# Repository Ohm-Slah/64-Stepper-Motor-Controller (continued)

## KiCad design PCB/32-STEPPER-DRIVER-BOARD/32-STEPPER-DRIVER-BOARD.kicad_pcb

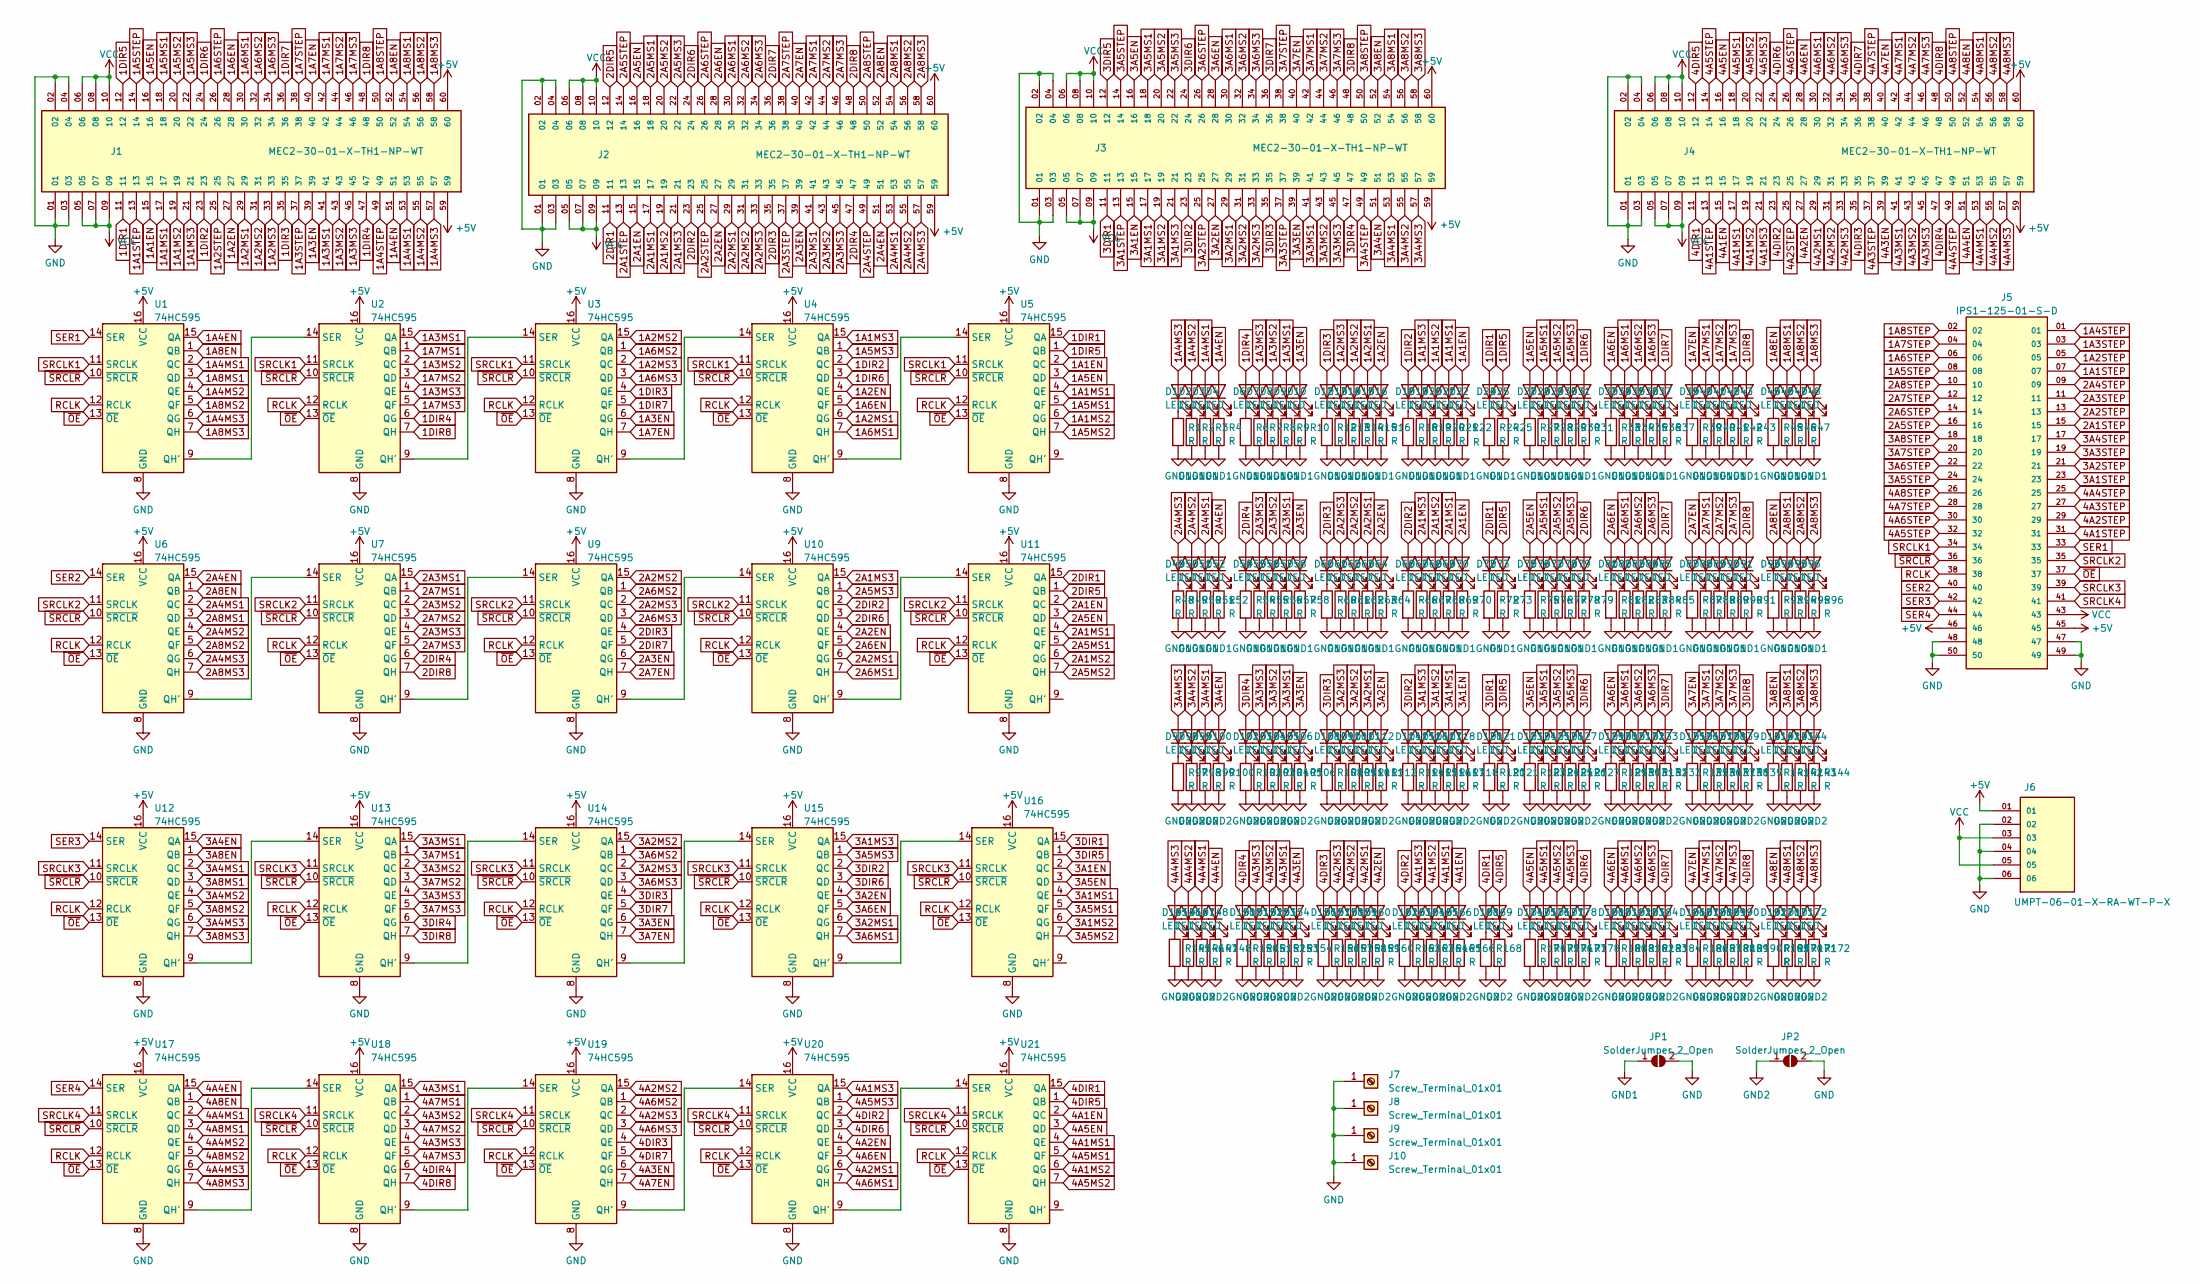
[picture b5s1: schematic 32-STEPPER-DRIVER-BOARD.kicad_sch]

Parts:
D1, D2, D3, D4, D6, D7, D8, D9, D10, D12, D13, D14, D15, D16, D18, D19, D20, D21, D22, D24, D25, D27, D28, D29, D30, D31, D33, D34, D35, D36, D37, D39, D40, D41, D42, D43, D45, D46, D47, D48, D49, D50, D51, D52, D54, D55, D56, D57, D58, D60, D61, D62, D63, D64, D66, D67, D68, D69, D70, D72, D73, D75, D76, D77, D78, D79, D81, D82, D83, D84, D85, D87, D88, D89, D90, D91, D93, D94, D95, D96, D97, D98, D99, D100, D102, D103, D104, D105, D106, D108, D109, D110, D111, D112, D114, D115, D116, D117, D118, D120, D121, D123, D124, D125, D126, D127, D129, D130, D131, D132, D133, D135, D136, D137, D138, D139, D141, D142, D143, D144, D145, D146, D147, D148, D150, D151, D152, D153, D154, D156, D157, D158, D159, D160, D162, D163, D164, D165, D166, D168, D169, D170, D171, D172, D174, D175, D176, D177, D178, D180, D181, D182, D183, D184, D186, D187, D188, D189, D190, D192: LED; LED_0603_1608Metric
J1, J2, J3, J4: MEC2-30-01-X-TH1-NP-WT; SAMTEC_MEC2-30-01-X-TH1-NP-WT; PARTREV F
J5: IPS1-125-01-S-D; SAMTEC_IPS1-125-01-S-D; PARTREV R
J6: UMPT-06-01-X-RA-WT-P-X; SAMTEC_UMPT-06-01-X-RA-WT-P-X; PARTREV 4
J7, J8, J9, J10: Screw_Terminal_01x01; MountingHole_2.2mm_M2_Pad
JP1, JP2: SolderJumper_2_Open; SolderJumper-2_P1.3mm_Open_RoundedPad1.0x1.5mm
R1, R2, R3, R4, R6, R7, R8, R9, R10, R12, R13, R14, R15, R16, R18, R19, R20, R21, R22, R24, R25, R27, R28, R29, R30, R31, R33, R34, R35, R36, R37, R39, R40, R41, R42, R43, R45, R46, R47, R48, R49, R50, R51, R52, R54, R55, R56, R57, R58, R60, R61, R62, R63, R64, R66, R67, R68, R69, R70, R72, R73, R75, R76, R77, R78, R79, R81, R82, R83, R84, R85, R87, R88, R89, R90, R91, R93, R94, R95, R96, R97, R98, R99, R100, R102, R103, R104, R105, R106, R108, R109, R110, R111, R112, R114, R115, R116, R117, R118, R120, R121, R123, R124, R125, R126, R127, R129, R130, R131, R132, R133, R135, R136, R137, R138, R139, R141, R142, R143, R144, R145, R146, R147, R148, R150, R151, R152, R153, R154, R156, R157, R158, R159, R160, R162, R163, R164, R165, R166, R168, R169, R170, R171, R172, R174, R175, R176, R177, R178, R180, R181, R182, R183, R184, R186, R187, R188, R189, R190, R192: R; R_0603_1608Metric
U1, U2, U3, U4, U5, U6, U7, U9, U10, U11, U12, U13, U14, U15, U16, U17, U18, U19, U20, U21: 74HC595; TSSOP-16_4.4x5mm_P0.65mm

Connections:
1A1EN: D22.2 (A), J1.15, U5.2 (QC)
1A1MS1: D21.2 (A), J1.17, U5.4 (QE)
1A1MS2: D20.2 (A), J1.19, U5.6 (QG)
1A1MS3: D19.2 (A), J1.21, U4.15 (QA)
1A1STEP: J1.13, J5.07
1A2EN: D16.2 (A), J1.27, U4.4 (QE)
1A2MS1: D15.2 (A), J1.29, U4.6 (QG)
1A2MS2: D14.2 (A), J1.31, U3.15 (QA)
1A2MS3: D13.2 (A), J1.33, U3.2 (QC)
1A2STEP: J1.25, J5.05
1A3EN: D10.2 (A), J1.39, U3.6 (QG)
1A3MS1: D9.2 (A), J1.41, U2.15 (QA)
1A3MS2: D8.2 (A), J1.43, U2.2 (QC)
1A3MS3: D7.2 (A), J1.45, U2.4 (QE)
1A3STEP: J1.37, J5.03
1A4EN: D4.2 (A), J1.51, U1.15 (QA)
1A4MS1: D3.2 (A), J1.53, U1.2 (QC)
1A4MS2: D2.2 (A), J1.55, U1.4 (QE)
1A4MS3: D1.2 (A), J1.57, U1.6 (QG)
1A4STEP: J1.49, J5.01
1A5EN: D27.2 (A), J1.16, U5.3 (QD)
1A5MS1: D28.2 (A), J1.18, U5.5 (QF)
1A5MS2: D29.2 (A), J1.20, U5.7 (QH)
1A5MS3: D30.2 (A), J1.22, U4.1 (QB)
1A5STEP: J1.14, J5.08
1A6EN: D33.2 (A), J1.28, U4.5 (QF)
1A6MS1: D34.2 (A), J1.30, U4.7 (QH)
1A6MS2: D35.2 (A), J1.32, U3.1 (QB)
1A6MS3: D36.2 (A), J1.34, U3.3 (QD)
1A6STEP: J1.26, J5.06
1A7EN: D39.2 (A), J1.40, U3.7 (QH)
1A7MS1: D40.2 (A), J1.42, U2.1 (QB)
1A7MS2: D41.2 (A), J1.44, U2.3 (QD)
1A7MS3: D42.2 (A), J1.46, U2.5 (QF)
1A7STEP: J1.38, J5.04
1A8EN: D45.2 (A), J1.52, U1.1 (QB)
1A8MS1: D46.2 (A), J1.54, U1.3 (QD)
1A8MS2: D47.2 (A), J1.56, U1.5 (QF)
1A8MS3: D48.2 (A), J1.58, U1.7 (QH)
1A8STEP: J1.50, J5.02
1DIR1: D24.2 (A), J1.11, U5.15 (QA)
1DIR2: D18.2 (A), J1.23, U4.2 (QC)
1DIR3: D12.2 (A), J1.35, U3.4 (QE)
1DIR4: D6.2 (A), J1.47, U2.6 (QG)
1DIR5: D25.2 (A), J1.12, U5.1 (QB)
1DIR6: D31.2 (A), J1.24, U4.3 (QD)
1DIR7: D37.2 (A), J1.36, U3.5 (QF)
1DIR8: D43.2 (A), J1.48, U2.7 (QH)
2A1EN: D70.2 (A), J2.15, U11.2 (QC)
2A1MS1: D69.2 (A), J2.17, U11.4 (QE)
2A1MS2: D68.2 (A), J2.19, U11.6 (QG)
2A1MS3: D67.2 (A), J2.21, U10.15 (QA)
2A1STEP: J2.13, J5.15
2A2EN: D64.2 (A), J2.27, U10.4 (QE)
2A2MS1: D63.2 (A), J2.29, U10.6 (QG)
2A2MS2: D62.2 (A), J2.31, U9.15 (QA)
2A2MS3: D61.2 (A), J2.33, U9.2 (QC)
2A2STEP: J2.25, J5.13
2A3EN: D58.2 (A), J2.39, U9.6 (QG)
2A3MS1: D57.2 (A), J2.41, U7.15 (QA)
2A3MS2: D56.2 (A), J2.43, U7.2 (QC)
2A3MS3: D55.2 (A), J2.45, U7.4 (QE)
2A3STEP: J2.37, J5.11
2A4EN: D52.2 (A), J2.51, U6.15 (QA)
2A4MS1: D51.2 (A), J2.53, U6.2 (QC)
2A4MS2: D50.2 (A), J2.55, U6.4 (QE)
2A4MS3: D49.2 (A), J2.57, U6.6 (QG)
2A4STEP: J2.49, J5.09
2A5EN: D75.2 (A), J2.16, U11.3 (QD)
2A5MS1: D76.2 (A), J2.18, U11.5 (QF)
2A5MS2: D77.2 (A), J2.20, U11.7 (QH)
2A5MS3: D78.2 (A), J2.22, U10.1 (QB)
2A5STEP: J2.14, J5.16
2A6EN: D81.2 (A), J2.28, U10.5 (QF)
2A6MS1: D82.2 (A), J2.30, U10.7 (QH)
2A6MS2: D83.2 (A), J2.32, U9.1 (QB)
2A6MS3: D84.2 (A), J2.34, U9.3 (QD)
2A6STEP: J2.26, J5.14
2A7EN: D87.2 (A), J2.40, U9.7 (QH)
2A7MS1: D88.2 (A), J2.42, U7.1 (QB)
2A7MS2: D89.2 (A), J2.44, U7.3 (QD)
2A7MS3: D90.2 (A), J2.46, U7.5 (QF)
2A7STEP: J2.38, J5.12
2A8EN: D93.2 (A), J2.52, U6.1 (QB)
2A8MS1: D94.2 (A), J2.54, U6.3 (QD)
2A8MS2: D95.2 (A), J2.56, U6.5 (QF)
2A8MS3: D96.2 (A), J2.58, U6.7 (QH)
2A8STEP: J2.50, J5.10
2DIR1: D72.2 (A), J2.11, U11.15 (QA)
2DIR2: D66.2 (A), J2.23, U10.2 (QC)
2DIR3: D60.2 (A), J2.35, U9.4 (QE)
2DIR4: D54.2 (A), J2.47, U7.6 (QG)
2DIR5: D73.2 (A), J2.12, U11.1 (QB)
2DIR6: D79.2 (A), J2.24, U10.3 (QD)
2DIR7: D85.2 (A), J2.36, U9.5 (QF)
2DIR8: D91.2 (A), J2.48, U7.7 (QH)
3A1EN: D118.2 (A), J3.15, U16.2 (QC)
3A1MS1: D117.2 (A), J3.17, U16.4 (QE)
3A1MS2: D116.2 (A), J3.19, U16.6 (QG)
3A1MS3: D115.2 (A), J3.21, U15.15 (QA)
3A1STEP: J3.13, J5.23
3A2EN: D112.2 (A), J3.27, U15.4 (QE)
3A2MS1: D111.2 (A), J3.29, U15.6 (QG)
3A2MS2: D110.2 (A), J3.31, U14.15 (QA)
3A2MS3: D109.2 (A), J3.33, U14.2 (QC)
3A2STEP: J3.25, J5.21
3A3EN: D106.2 (A), J3.39, U14.6 (QG)
3A3MS1: D105.2 (A), J3.41, U13.15 (QA)
3A3MS2: D104.2 (A), J3.43, U13.2 (QC)
3A3MS3: D103.2 (A), J3.45, U13.4 (QE)
3A3STEP: J3.37, J5.19
3A4EN: D100.2 (A), J3.51, U12.15 (QA)
3A4MS1: D99.2 (A), J3.53, U12.2 (QC)
3A4MS2: D98.2 (A), J3.55, U12.4 (QE)
3A4MS3: D97.2 (A), J3.57, U12.6 (QG)
3A4STEP: J3.49, J5.17
3A5EN: D123.2 (A), J3.16, U16.3 (QD)
3A5MS1: D124.2 (A), J3.18, U16.5 (QF)
3A5MS2: D125.2 (A), J3.20, U16.7 (QH)
3A5MS3: D126.2 (A), J3.22, U15.1 (QB)
3A5STEP: J3.14, J5.24
3A6EN: D129.2 (A), J3.28, U15.5 (QF)
3A6MS1: D130.2 (A), J3.30, U15.7 (QH)
3A6MS2: D131.2 (A), J3.32, U14.1 (QB)
3A6MS3: D132.2 (A), J3.34, U14.3 (QD)
3A6STEP: J3.26, J5.22
3A7EN: D135.2 (A), J3.40, U14.7 (QH)
3A7MS1: D136.2 (A), J3.42, U13.1 (QB)
3A7MS2: D137.2 (A), J3.44, U13.3 (QD)
3A7MS3: D138.2 (A), J3.46, U13.5 (QF)
3A7STEP: J3.38, J5.20
3A8EN: D141.2 (A), J3.52, U12.1 (QB)
3A8MS1: D142.2 (A), J3.54, U12.3 (QD)
3A8MS2: D143.2 (A), J3.56, U12.5 (QF)
3A8MS3: D144.2 (A), J3.58, U12.7 (QH)
3A8STEP: J3.50, J5.18
3DIR1: D120.2 (A), J3.11, U16.15 (QA)
3DIR2: D114.2 (A), J3.23, U15.2 (QC)
3DIR3: D108.2 (A), J3.35, U14.4 (QE)
3DIR4: D102.2 (A), J3.47, U13.6 (QG)
3DIR5: D121.2 (A), J3.12, U16.1 (QB)
3DIR6: D127.2 (A), J3.24, U15.3 (QD)
3DIR7: D133.2 (A), J3.36, U14.5 (QF)
3DIR8: D139.2 (A), J3.48, U13.7 (QH)
4A1EN: D166.2 (A), J4.15, U21.2 (QC)
4A1MS1: D165.2 (A), J4.17, U21.4 (QE)
4A1MS2: D164.2 (A), J4.19, U21.6 (QG)
4A1MS3: D163.2 (A), J4.21, U20.15 (QA)
4A1STEP: J4.13, J5.31
4A2EN: D160.2 (A), J4.27, U20.4 (QE)
4A2MS1: D159.2 (A), J4.29, U20.6 (QG)
4A2MS2: D158.2 (A), J4.31, U19.15 (QA)
4A2MS3: D157.2 (A), J4.33, U19.2 (QC)
4A2STEP: J4.25, J5.29
4A3EN: D154.2 (A), J4.39, U19.6 (QG)
4A3MS1: D153.2 (A), J4.41, U18.15 (QA)
4A3MS2: D152.2 (A), J4.43, U18.2 (QC)
4A3MS3: D151.2 (A), J4.45, U18.4 (QE)
4A3STEP: J4.37, J5.27
4A4EN: D148.2 (A), J4.51, U17.15 (QA)
4A4MS1: D147.2 (A), J4.53, U17.2 (QC)
4A4MS2: D146.2 (A), J4.55, U17.4 (QE)
4A4MS3: D145.2 (A), J4.57, U17.6 (QG)
4A4STEP: J4.49, J5.25
4A5EN: D174.2 (A), J4.16, U21.3 (QD)
4A5MS1: D175.2 (A), J4.18, U21.5 (QF)
4A5MS2: D176.2 (A), J4.20, U21.7 (QH)
4A5MS3: D177.2 (A), J4.22, U20.1 (QB)
4A5STEP: J4.14, J5.32
4A6EN: D180.2 (A), J4.28, U20.5 (QF)
4A6MS1: D181.2 (A), J4.30, U20.7 (QH)
4A6MS2: D182.2 (A), J4.32, U19.1 (QB)
4A6MS3: D183.2 (A), J4.34, U19.3 (QD)
4A6STEP: J4.26, J5.30
4A7EN: D186.2 (A), J4.40, U19.7 (QH)
4A7MS1: D187.2 (A), J4.42, U18.1 (QB)
4A7MS2: D188.2 (A), J4.44, U18.3 (QD)
4A7MS3: D189.2 (A), J4.46, U18.5 (QF)
4A7STEP: J4.38, J5.28
4A8EN: D192.2 (A), J4.52, U17.1 (QB)
4A8MS1: D170.2 (A), J4.54, U17.3 (QD)
4A8MS2: D171.2 (A), J4.56, U17.5 (QF)
4A8MS3: D172.2 (A), J4.58, U17.7 (QH)
4A8STEP: J4.50, J5.26
4DIR1: D168.2 (A), J4.11, U21.15 (QA)
4DIR2: D162.2 (A), J4.23, U20.2 (QC)
4DIR3: D156.2 (A), J4.35, U19.4 (QE)
4DIR4: D150.2 (A), J4.47, U18.6 (QG)
4DIR5: D169.2 (A), J4.12, U21.1 (QB)
4DIR6: D178.2 (A), J4.24, U20.3 (QD)
4DIR7: D184.2 (A), J4.36, U19.5 (QF)
4DIR8: D190.2 (A), J4.48, U18.7 (QH)
+5V: J1.59, J1.60, J2.59, J2.60, J3.59, J3.60, J4.59, J4.60, J5.45, J5.46, J6.01, U1.16 (VCC), U2.16 (VCC), U3.16 (VCC), U4.16 (VCC), U5.16 (VCC), U6.16 (VCC), U7.16 (VCC), U9.16 (VCC), U10.16 (VCC), U11.16 (VCC), U12.16 (VCC), U13.16 (VCC), U14.16 (VCC), U15.16 (VCC), U16.16 (VCC), U17.16 (VCC), U18.16 (VCC), U19.16 (VCC), U20.16 (VCC), U21.16 (VCC)
GND: J1.01, J1.02, J1.03, J1.04, J2.01, J2.02, J2.03, J2.04, J3.01, J3.02, J3.03, J3.04, J4.01, J4.02, J4.03, J4.04, J5.47, J5.48, J5.49, J5.50, J6.02, J6.04, J6.06, J7.1, J8.1, J9.1, J10.1, JP1.2 (B), JP2.2 (B), U1.8 (GND), U2.8 (GND), U3.8 (GND), U4.8 (GND), U5.8 (GND), U6.8 (GND), U7.8 (GND), U9.8 (GND), U10.8 (GND), U11.8 (GND), U12.8 (GND), U13.8 (GND), U14.8 (GND), U15.8 (GND), U16.8 (GND), U17.8 (GND), U18.8 (GND), U19.8 (GND), U20.8 (GND), U21.8 (GND)
GND1: JP1.1 (A), R1.2, R2.2, R3.2, R4.2, R6.2, R7.2, R8.2, R9.2, R10.2, R12.2, R13.2, R14.2, R15.2, R16.2, R18.2, R19.2, R20.2, R21.2, R22.2, R24.2, R25.2, R27.2, R28.2, R29.2, R30.2, R31.2, R33.2, R34.2, R35.2, R36.2, R37.2, R39.2, R40.2, R41.2, R42.2, R43.2, R45.2, R46.2, R47.2, R48.2, R49.2, R50.2, R51.2, R52.2, R54.2, R55.2, R56.2, R57.2, R58.2, R60.2, R61.2, R62.2, R63.2, R64.2, R66.2, R67.2, R68.2, R69.2, R70.2, R72.2, R73.2, R75.2, R76.2, R77.2, R78.2, R79.2, R81.2, R82.2, R83.2, R84.2, R85.2, R87.2, R88.2, R89.2, R90.2, R91.2, R93.2, R94.2, R95.2, R96.2
GND2: JP2.1 (A), R97.2, R98.2, R99.2, R100.2, R102.2, R103.2, R104.2, R105.2, R106.2, R108.2, R109.2, R110.2, R111.2, R112.2, R114.2, R115.2, R116.2, R117.2, R118.2, R120.2, R121.2, R123.2, R124.2, R125.2, R126.2, R127.2, R129.2, R130.2, R131.2, R132.2, R133.2, R135.2, R136.2, R137.2, R138.2, R139.2, R141.2, R142.2, R143.2, R144.2, R145.2, R146.2, R147.2, R148.2, R150.2, R151.2, R152.2, R153.2, R154.2, R156.2, R157.2, R158.2, R159.2, R160.2, R162.2, R163.2, R164.2, R165.2, R166.2, R168.2, R169.2, R170.2, R171.2, R172.2, R174.2, R175.2, R176.2, R177.2, R178.2, R180.2, R181.2, R182.2, R183.2, R184.2, R186.2, R187.2, R188.2, R189.2, R190.2, R192.2
unnamed: D1.1 (K), R1.1
unnamed: D2.1 (K), R2.1
unnamed: D3.1 (K), R3.1
unnamed: D4.1 (K), R4.1
unnamed: D6.1 (K), R6.1
unnamed: D7.1 (K), R7.1
unnamed: D8.1 (K), R8.1
unnamed: D9.1 (K), R9.1
unnamed: D10.1 (K), R10.1
unnamed: D12.1 (K), R12.1
unnamed: D13.1 (K), R13.1
unnamed: D14.1 (K), R14.1
unnamed: D15.1 (K), R15.1
unnamed: D16.1 (K), R16.1
unnamed: D18.1 (K), R18.1
unnamed: D19.1 (K), R19.1
unnamed: D20.1 (K), R20.1
unnamed: D21.1 (K), R21.1
unnamed: D22.1 (K), R22.1
unnamed: D24.1 (K), R24.1
unnamed: D25.1 (K), R25.1
unnamed: D27.1 (K), R27.1
unnamed: D28.1 (K), R28.1
unnamed: D29.1 (K), R29.1
unnamed: D30.1 (K), R30.1
unnamed: D31.1 (K), R31.1
unnamed: D33.1 (K), R33.1
unnamed: D34.1 (K), R34.1
unnamed: D35.1 (K), R35.1
unnamed: D36.1 (K), R36.1
unnamed: D37.1 (K), R37.1
unnamed: D39.1 (K), R39.1
unnamed: D40.1 (K), R40.1
unnamed: D41.1 (K), R41.1
unnamed: D42.1 (K), R42.1
unnamed: D43.1 (K), R43.1
unnamed: D45.1 (K), R45.1
unnamed: D46.1 (K), R46.1
unnamed: D47.1 (K), R47.1
unnamed: D48.1 (K), R48.1
unnamed: D49.1 (K), R49.1
unnamed: D50.1 (K), R50.1
unnamed: D51.1 (K), R51.1
unnamed: D52.1 (K), R52.1
unnamed: D54.1 (K), R54.1
unnamed: D55.1 (K), R55.1
unnamed: D56.1 (K), R56.1
unnamed: D57.1 (K), R57.1
unnamed: D58.1 (K), R58.1
unnamed: D60.1 (K), R60.1
unnamed: D61.1 (K), R61.1
unnamed: D62.1 (K), R62.1
unnamed: D63.1 (K), R63.1
unnamed: D64.1 (K), R64.1
unnamed: D66.1 (K), R66.1
unnamed: D67.1 (K), R67.1
unnamed: D68.1 (K), R68.1
unnamed: D69.1 (K), R69.1
unnamed: D70.1 (K), R70.1
unnamed: D72.1 (K), R72.1
unnamed: D73.1 (K), R73.1
unnamed: D75.1 (K), R75.1
unnamed: D76.1 (K), R76.1
unnamed: D77.1 (K), R77.1
unnamed: D78.1 (K), R78.1
unnamed: D79.1 (K), R79.1
unnamed: D81.1 (K), R81.1
unnamed: D82.1 (K), R82.1
unnamed: D83.1 (K), R83.1
unnamed: D84.1 (K), R84.1
unnamed: D85.1 (K), R85.1
unnamed: D87.1 (K), R87.1
unnamed: D88.1 (K), R88.1
unnamed: D89.1 (K), R89.1
unnamed: D90.1 (K), R90.1
unnamed: D91.1 (K), R91.1
unnamed: D93.1 (K), R93.1
unnamed: D94.1 (K), R94.1
unnamed: D95.1 (K), R95.1
unnamed: D96.1 (K), R96.1
unnamed: D97.1 (K), R97.1
unnamed: D98.1 (K), R98.1
unnamed: D99.1 (K), R99.1
unnamed: D100.1 (K), R100.1
unnamed: D102.1 (K), R102.1
unnamed: D103.1 (K), R103.1
unnamed: D104.1 (K), R104.1
unnamed: D105.1 (K), R105.1
unnamed: D106.1 (K), R106.1
unnamed: D108.1 (K), R108.1
unnamed: D109.1 (K), R109.1
unnamed: D110.1 (K), R110.1
unnamed: D111.1 (K), R111.1
unnamed: D112.1 (K), R112.1
unnamed: D114.1 (K), R114.1
unnamed: D115.1 (K), R115.1
unnamed: D116.1 (K), R116.1
unnamed: D117.1 (K), R117.1
unnamed: D118.1 (K), R118.1
unnamed: D120.1 (K), R120.1
unnamed: D121.1 (K), R121.1
unnamed: D123.1 (K), R123.1
unnamed: D124.1 (K), R124.1
unnamed: D125.1 (K), R125.1
unnamed: D126.1 (K), R126.1
unnamed: D127.1 (K), R127.1
unnamed: D129.1 (K), R129.1
unnamed: D130.1 (K), R130.1
unnamed: D131.1 (K), R131.1
unnamed: D132.1 (K), R132.1
unnamed: D133.1 (K), R133.1
unnamed: D135.1 (K), R135.1
unnamed: D136.1 (K), R136.1
unnamed: D137.1 (K), R137.1
unnamed: D138.1 (K), R138.1
unnamed: D139.1 (K), R139.1
unnamed: D141.1 (K), R141.1
unnamed: D142.1 (K), R142.1
unnamed: D143.1 (K), R143.1
unnamed: D144.1 (K), R144.1
unnamed: D145.1 (K), R145.1
unnamed: D146.1 (K), R146.1
unnamed: D147.1 (K), R147.1
unnamed: D148.1 (K), R148.1
unnamed: D150.1 (K), R150.1
unnamed: D151.1 (K), R151.1
unnamed: D152.1 (K), R152.1
unnamed: D153.1 (K), R153.1
unnamed: D154.1 (K), R154.1
unnamed: D156.1 (K), R156.1
unnamed: D157.1 (K), R157.1
unnamed: D158.1 (K), R158.1
unnamed: D159.1 (K), R159.1
unnamed: D160.1 (K), R160.1
unnamed: D162.1 (K), R162.1
unnamed: D163.1 (K), R163.1
unnamed: D164.1 (K), R164.1
unnamed: D165.1 (K), R165.1
unnamed: D166.1 (K), R166.1
unnamed: D168.1 (K), R168.1
unnamed: D169.1 (K), R169.1
unnamed: D170.1 (K), R170.1
unnamed: D171.1 (K), R171.1
unnamed: D172.1 (K), R172.1
unnamed: D174.1 (K), R174.1
unnamed: D175.1 (K), R175.1
unnamed: D176.1 (K), R176.1
unnamed: D177.1 (K), R177.1
unnamed: D178.1 (K), R178.1
unnamed: D180.1 (K), R180.1
unnamed: D181.1 (K), R181.1
unnamed: D182.1 (K), R182.1
unnamed: D183.1 (K), R183.1
unnamed: D184.1 (K), R184.1
unnamed: D186.1 (K), R186.1
unnamed: D187.1 (K), R187.1
unnamed: D188.1 (K), R188.1
unnamed: D189.1 (K), R189.1
unnamed: D190.1 (K), R190.1
unnamed: D192.1 (K), R192.1
unnamed: U1.9 (QH'), U2.14 (SER)
unnamed: U2.9 (QH'), U3.14 (SER)
unnamed: U3.9 (QH'), U4.14 (SER)
unnamed: U4.9 (QH'), U5.14 (SER)
unnamed: U6.9 (QH'), U7.14 (SER)
unnamed: U7.9 (QH'), U9.14 (SER)
unnamed: U10.9 (QH'), U11.14 (SER)
unnamed: U9.9 (QH'), U10.14 (SER)
unnamed: U12.9 (QH'), U13.14 (SER)
unnamed: U13.9 (QH'), U14.14 (SER)
unnamed: U14.9 (QH'), U15.14 (SER)
unnamed: U15.9 (QH'), U16.14 (SER)
unnamed: U17.9 (QH'), U18.14 (SER)
unnamed: U18.9 (QH'), U19.14 (SER)
unnamed: U19.9 (QH'), U20.14 (SER)
unnamed: U20.9 (QH'), U21.14 (SER)
RCLK: J5.38, U1.12 (RCLK), U2.12 (RCLK), U3.12 (RCLK), U4.12 (RCLK), U5.12 (RCLK), U6.12 (RCLK), U7.12 (RCLK), U9.12 (RCLK), U10.12 (RCLK), U11.12 (RCLK), U12.12 (RCLK), U13.12 (RCLK), U14.12 (RCLK), U15.12 (RCLK), U16.12 (RCLK), U17.12 (RCLK), U18.12 (RCLK), U19.12 (RCLK), U20.12 (RCLK), U21.12 (RCLK)
SER1: J5.33, U1.14 (SER)
SER2: J5.40, U6.14 (SER)
SER3: J5.42, U12.14 (SER)
SER4: J5.44, U17.14 (SER)
SRCLK1: J5.34, U1.11 (SRCLK), U2.11 (SRCLK), U3.11 (SRCLK), U4.11 (SRCLK), U5.11 (SRCLK)
SRCLK2: J5.35, U6.11 (SRCLK), U7.11 (SRCLK), U9.11 (SRCLK), U10.11 (SRCLK), U11.11 (SRCLK)
SRCLK3: J5.39, U12.11 (SRCLK), U13.11 (SRCLK), U14.11 (SRCLK), U15.11 (SRCLK), U16.11 (SRCLK)
SRCLK4: J5.41, U17.11 (SRCLK), U18.11 (SRCLK), U19.11 (SRCLK), U20.11 (SRCLK), U21.11 (SRCLK)
VCC: J1.05, J1.06, J1.07, J1.08, J1.09, J1.10, J2.05, J2.06, J2.07, J2.08, J2.09, J2.10, J3.05, J3.06, J3.07, J3.08, J3.09, J3.10, J4.05, J4.06, J4.07, J4.08, J4.09, J4.10, J5.43, J6.03, J6.05
~OE: J5.37, U1.13 (~OE), U2.13 (~OE), U3.13 (~OE), U4.13 (~OE), U5.13 (~OE), U6.13 (~OE), U7.13 (~OE), U9.13 (~OE), U10.13 (~OE), U11.13 (~OE), U12.13 (~OE), U13.13 (~OE), U14.13 (~OE), U15.13 (~OE), U16.13 (~OE), U17.13 (~OE), U18.13 (~OE), U19.13 (~OE), U20.13 (~OE), U21.13 (~OE)
~SRCLR: J5.36, U1.10 (~SRCLR), U2.10 (~SRCLR), U3.10 (~SRCLR), U4.10 (~SRCLR), U5.10 (~SRCLR), U6.10 (~SRCLR), U7.10 (~SRCLR), U9.10 (~SRCLR), U10.10 (~SRCLR), U11.10 (~SRCLR), U12.10 (~SRCLR), U13.10 (~SRCLR), U14.10 (~SRCLR), U15.10 (~SRCLR), U16.10 (~SRCLR), U17.10 (~SRCLR), U18.10 (~SRCLR), U19.10 (~SRCLR), U20.10 (~SRCLR), U21.10 (~SRCLR)

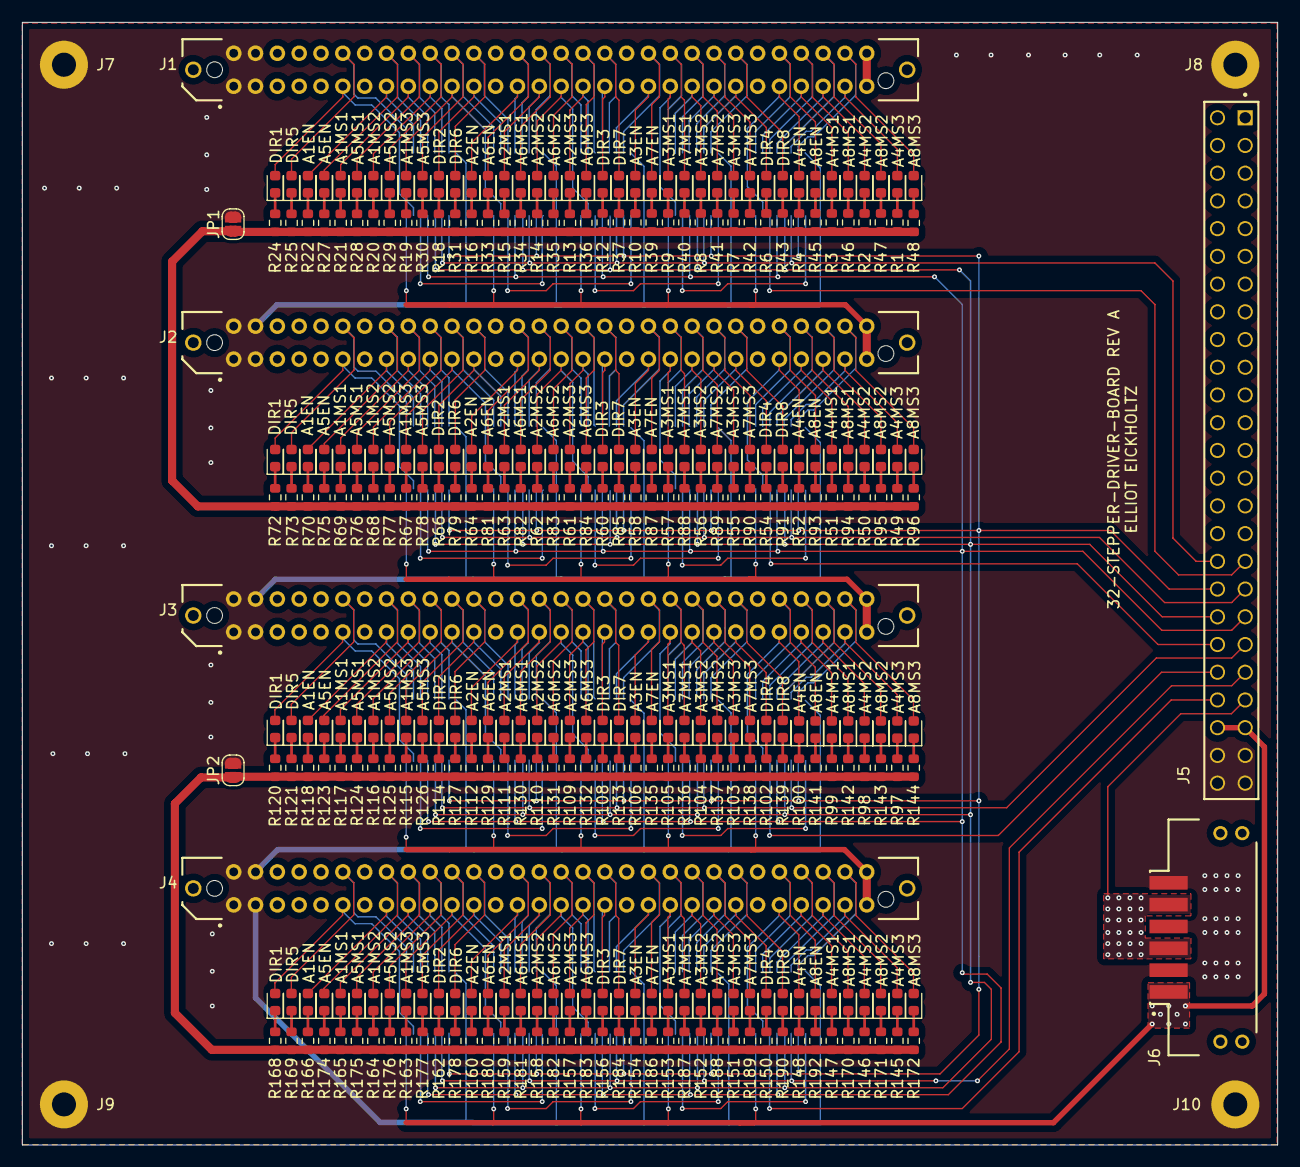
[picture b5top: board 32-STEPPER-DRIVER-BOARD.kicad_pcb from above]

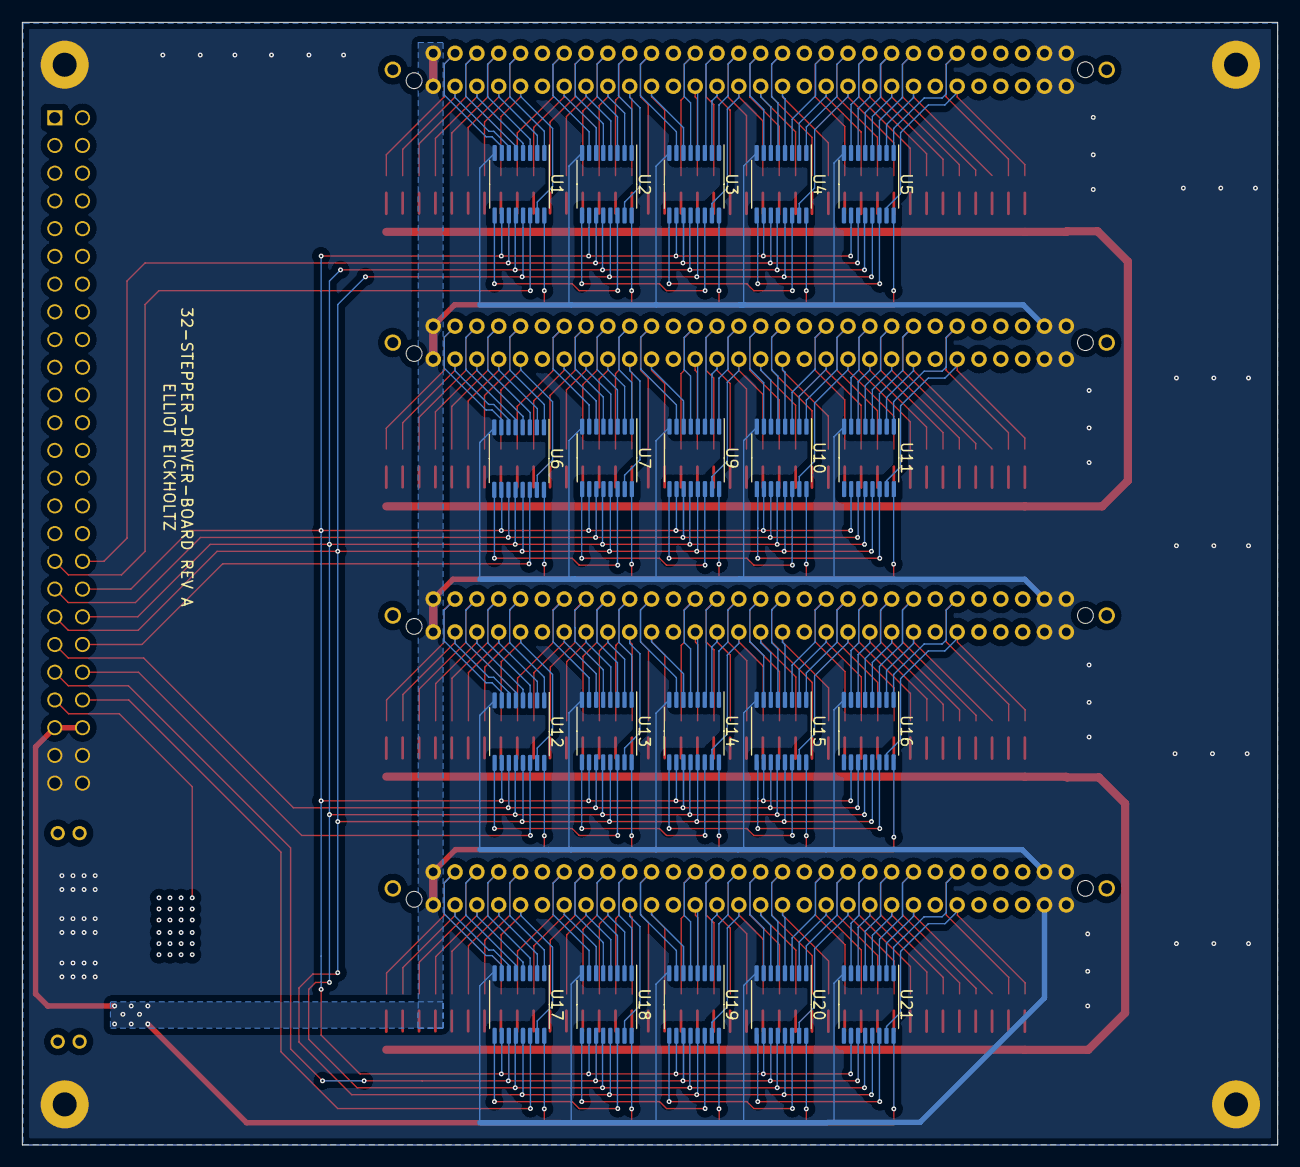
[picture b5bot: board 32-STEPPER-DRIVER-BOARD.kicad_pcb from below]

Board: 4 copper layers, 115.0 x 102.8 mm, 352 parts (20 on the bottom side), 384 nets.

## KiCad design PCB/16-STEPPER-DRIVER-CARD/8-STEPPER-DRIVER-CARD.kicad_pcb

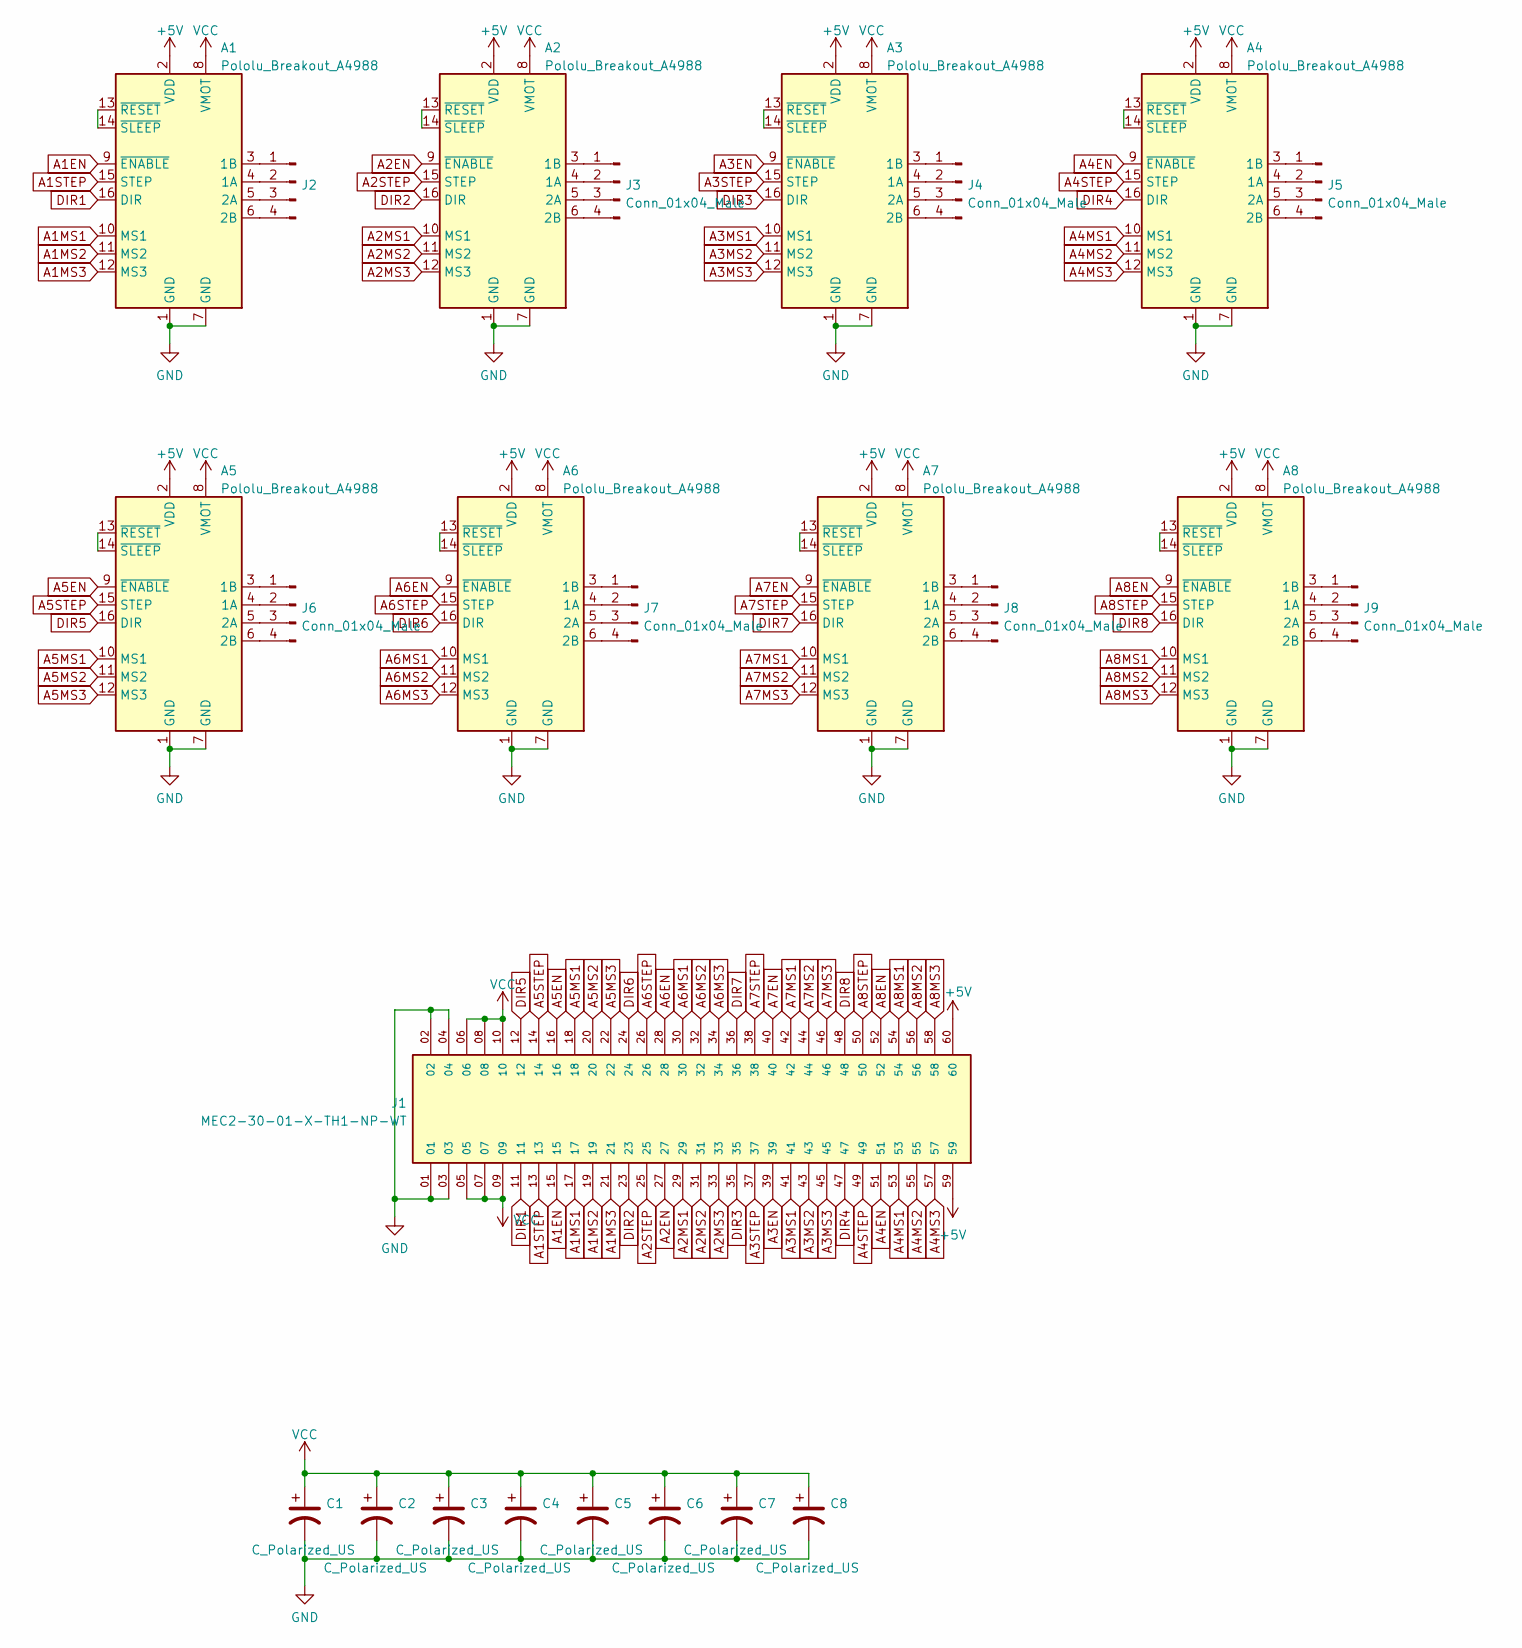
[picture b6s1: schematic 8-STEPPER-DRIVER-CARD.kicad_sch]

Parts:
A1, A2, A3, A4, A5, A6, A7, A8: Pololu_Breakout_A4988; Pololu_Breakout-16_15.2x20.3mm
C1, C2, C3, C4, C5, C6, C7, C8: C_Polarized_US; CP_Radial_D6.3mm_P2.50mm
J1: MEC2-30-01-X-TH1-NP-WT; MEC2-30-01-J-TH1-NP-WT-EDGECARD; PARTREV F
J2: (no value)
J3, J4, J5, J6, J7, J8, J9: Conn_01x04_Male

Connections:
+5V: A1.2 (VDD), A2.2 (VDD), A3.2 (VDD), A4.2 (VDD), A5.2 (VDD), A6.2 (VDD), A7.2 (VDD), A8.2 (VDD), J1.59, J1.60
A1EN: A1.9 (~ENABLE), J1.15
A1MS1: A1.10 (MS1), J1.17
A1MS2: A1.11 (MS2), J1.19
A1MS3: A1.12 (MS3), J1.21
A1STEP: A1.15 (STEP), J1.13
A2EN: A2.9 (~ENABLE), J1.27
A2MS1: A2.10 (MS1), J1.29
A2MS2: A2.11 (MS2), J1.31
A2MS3: A2.12 (MS3), J1.33
A2STEP: A2.15 (STEP), J1.25
A3EN: A3.9 (~ENABLE), J1.39
A3MS1: A3.10 (MS1), J1.41
A3MS2: A3.11 (MS2), J1.43
A3MS3: A3.12 (MS3), J1.45
A3STEP: A3.15 (STEP), J1.37
A4EN: A4.9 (~ENABLE), J1.51
A4MS1: A4.10 (MS1), J1.53
A4MS2: A4.11 (MS2), J1.55
A4MS3: A4.12 (MS3), J1.57
A4STEP: A4.15 (STEP), J1.49
A5EN: A5.9 (~ENABLE), J1.16
A5MS1: A5.10 (MS1), J1.18
A5MS2: A5.11 (MS2), J1.20
A5MS3: A5.12 (MS3), J1.22
A5STEP: A5.15 (STEP), J1.14
A6EN: A6.9 (~ENABLE), J1.28
A6MS1: A6.10 (MS1), J1.30
A6MS2: A6.11 (MS2), J1.32
A6MS3: A6.12 (MS3), J1.34
A6STEP: A6.15 (STEP), J1.26
A7EN: A7.9 (~ENABLE), J1.40
A7MS1: A7.10 (MS1), J1.42
A7MS2: A7.11 (MS2), J1.44
A7MS3: A7.12 (MS3), J1.46
A7STEP: A7.15 (STEP), J1.38
A8EN: A8.9 (~ENABLE), J1.52
A8MS1: A8.10 (MS1), J1.54
A8MS2: A8.11 (MS2), J1.56
A8MS3: A8.12 (MS3), J1.58
A8STEP: A8.15 (STEP), J1.50
DIR1: A1.16 (DIR), J1.11
DIR2: A2.16 (DIR), J1.23
DIR3: A3.16 (DIR), J1.35
DIR4: A4.16 (DIR), J1.47
DIR5: A5.16 (DIR), J1.12
DIR6: A6.16 (DIR), J1.24
DIR7: A7.16 (DIR), J1.36
DIR8: A8.16 (DIR), J1.48
GND: A1.1 (GND), A1.7 (GND), A2.1 (GND), A2.7 (GND), A3.1 (GND), A3.7 (GND), A4.1 (GND), A4.7 (GND), A5.1 (GND), A5.7 (GND), A6.1 (GND), A6.7 (GND), A7.1 (GND), A7.7 (GND), A8.1 (GND), A8.7 (GND), C1.2, C2.2, C3.2, C4.2, C5.2, C6.2, C7.2, C8.2, J1.01, J1.02, J1.03, J1.04
unnamed: A1.3 (1B), J2.1
unnamed: A1.4 (1A), J2.2
unnamed: A1.5 (2A), J2.3
unnamed: A1.6 (2B), J2.4
unnamed: A1.13 (~RESET), A1.14 (~SLEEP)
unnamed: A2.3 (1B), J3.1
unnamed: A2.4 (1A), J3.2
unnamed: A2.5 (2A), J3.3
unnamed: A2.6 (2B), J3.4
unnamed: A2.13 (~RESET), A2.14 (~SLEEP)
unnamed: A3.3 (1B), J4.1
unnamed: A3.4 (1A), J4.2
unnamed: A3.5 (2A), J4.3
unnamed: A3.6 (2B), J4.4
unnamed: A3.13 (~RESET), A3.14 (~SLEEP)
unnamed: A4.3 (1B), J5.1
unnamed: A4.4 (1A), J5.2
unnamed: A4.5 (2A), J5.3
unnamed: A4.6 (2B), J5.4
unnamed: A4.13 (~RESET), A4.14 (~SLEEP)
unnamed: A5.3 (1B), J6.1
unnamed: A5.4 (1A), J6.2
unnamed: A5.5 (2A), J6.3
unnamed: A5.6 (2B), J6.4
unnamed: A5.13 (~RESET), A5.14 (~SLEEP)
unnamed: A6.3 (1B), J7.1
unnamed: A6.4 (1A), J7.2
unnamed: A6.5 (2A), J7.3
unnamed: A6.6 (2B), J7.4
unnamed: A6.13 (~RESET), A6.14 (~SLEEP)
unnamed: A7.3 (1B), J8.1
unnamed: A7.4 (1A), J8.2
unnamed: A7.5 (2A), J8.3
unnamed: A7.6 (2B), J8.4
unnamed: A7.13 (~RESET), A7.14 (~SLEEP)
unnamed: A8.3 (1B), J9.1
unnamed: A8.4 (1A), J9.2
unnamed: A8.5 (2A), J9.3
unnamed: A8.6 (2B), J9.4
unnamed: A8.13 (~RESET), A8.14 (~SLEEP)
VCC: A1.8 (VMOT), A2.8 (VMOT), A3.8 (VMOT), A4.8 (VMOT), A5.8 (VMOT), A6.8 (VMOT), A7.8 (VMOT), A8.8 (VMOT), C1.1, C2.1, C3.1, C4.1, C5.1, C6.1, C7.1, C8.1, J1.05, J1.06, J1.07, J1.08, J1.09, J1.10

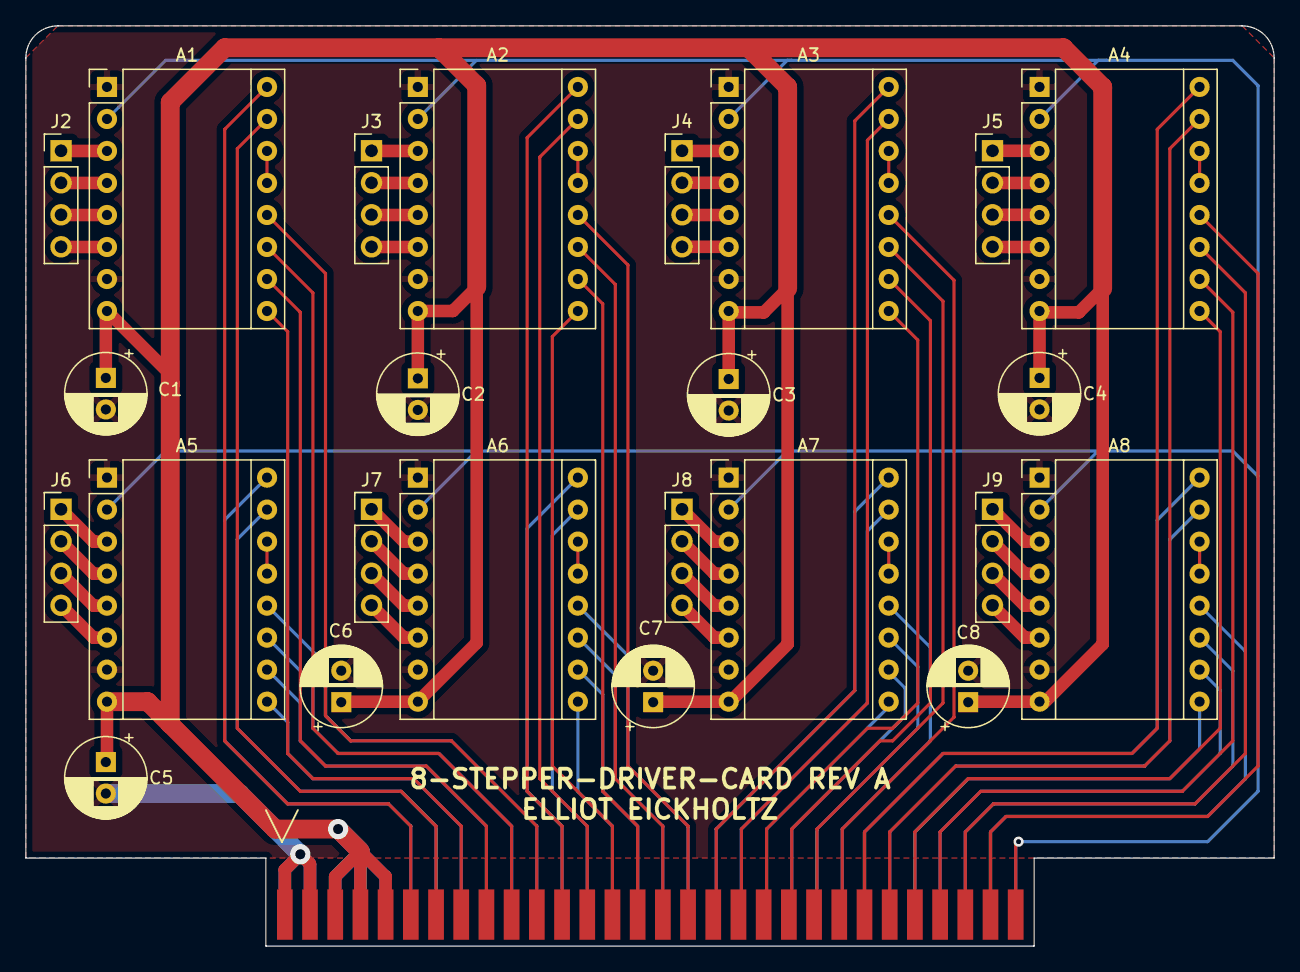
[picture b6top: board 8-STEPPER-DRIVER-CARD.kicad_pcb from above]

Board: 2 copper layers, 99.1 x 73.0 mm, 25 parts (0 on the bottom side), 91 nets.
